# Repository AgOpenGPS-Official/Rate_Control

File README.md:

### [Nano RC12-3](Nano/RC12-3)
- uses a Nano (with ENC28J60 Ethernet shield) & an on-board mounted Cytron for rate control
	- 1 or 2 [MD13S](https://www.cytron.io/p-13amp-6v-30v-dc-motor-driver) for rate control
- self assembled through-hole board, least expensive
- controls two rates
- can be connected to a relay module with a 20 pin cable or dupont connectors
- work switch
- pressure switch
- [OSHPARK]([https://oshpark.com/shared_projects/UU8e90h9](https://oshpark.com/shared_projects/fRBlR1Se)

#
### [Teensy 4.1 RC11-2](Teensy/RC11-2_PCB)
- uses a Teensy & an on-board mounted Cytron for rate control
	- either (1) [MD13S](https://www.cytron.io/p-13amp-6v-30v-dc-motor-driver) for single rate control
 	- or (1) [MDD10A](https://www.cytron.io/p-10amp-5v-30v-dc-motor-driver-2-channels) for dual rate control
- small components are surface mount parts
- Teensy Ethernet 
- can control two rates and eight sections
	- 8 relays (SPDT 12V output)
	- (1) 5V or 12V analog (pressure) input, potentiometer adjustable filtering
	- (2) optically isolated digital (rate/pulse) inputs (5V or 12V)
- 3.3V I2C headers (Qwiic)
	- supports optional external RelayDriver5 I2C board
 - work switch
 - canbus

#
### [ESP32 RC15](ESP32/RC15)
- uses an ESP32 (optional W5500 Ethernet Module)
- mostly surface mount parts
- can control two rates and 7-14 sections
	- (2) DRV8870 motor drivers with reversible outputs for rates
	- (7) DRV8870 motor drivers for either 7 reversible (motorized ball valve) outputs or 14 single ended (high or low) section outputs
- (4) 5V analog inputs (or 2 differential inputs)
- (2) optically isolated digital (rate/pulse) inputs, up to 12V
- RS485 chip & header
- 3.3V I2C header
	- supports optional external RelayDriver5 I2C board

#
### [RelayDriver5](RelayDriver5)
- PCA9535 based I2C IO expander
- designed to plug into 8 or 16 channel relay board with Qwiic cable

#
### Firmware
https://github.com/SK21/AOG_RC

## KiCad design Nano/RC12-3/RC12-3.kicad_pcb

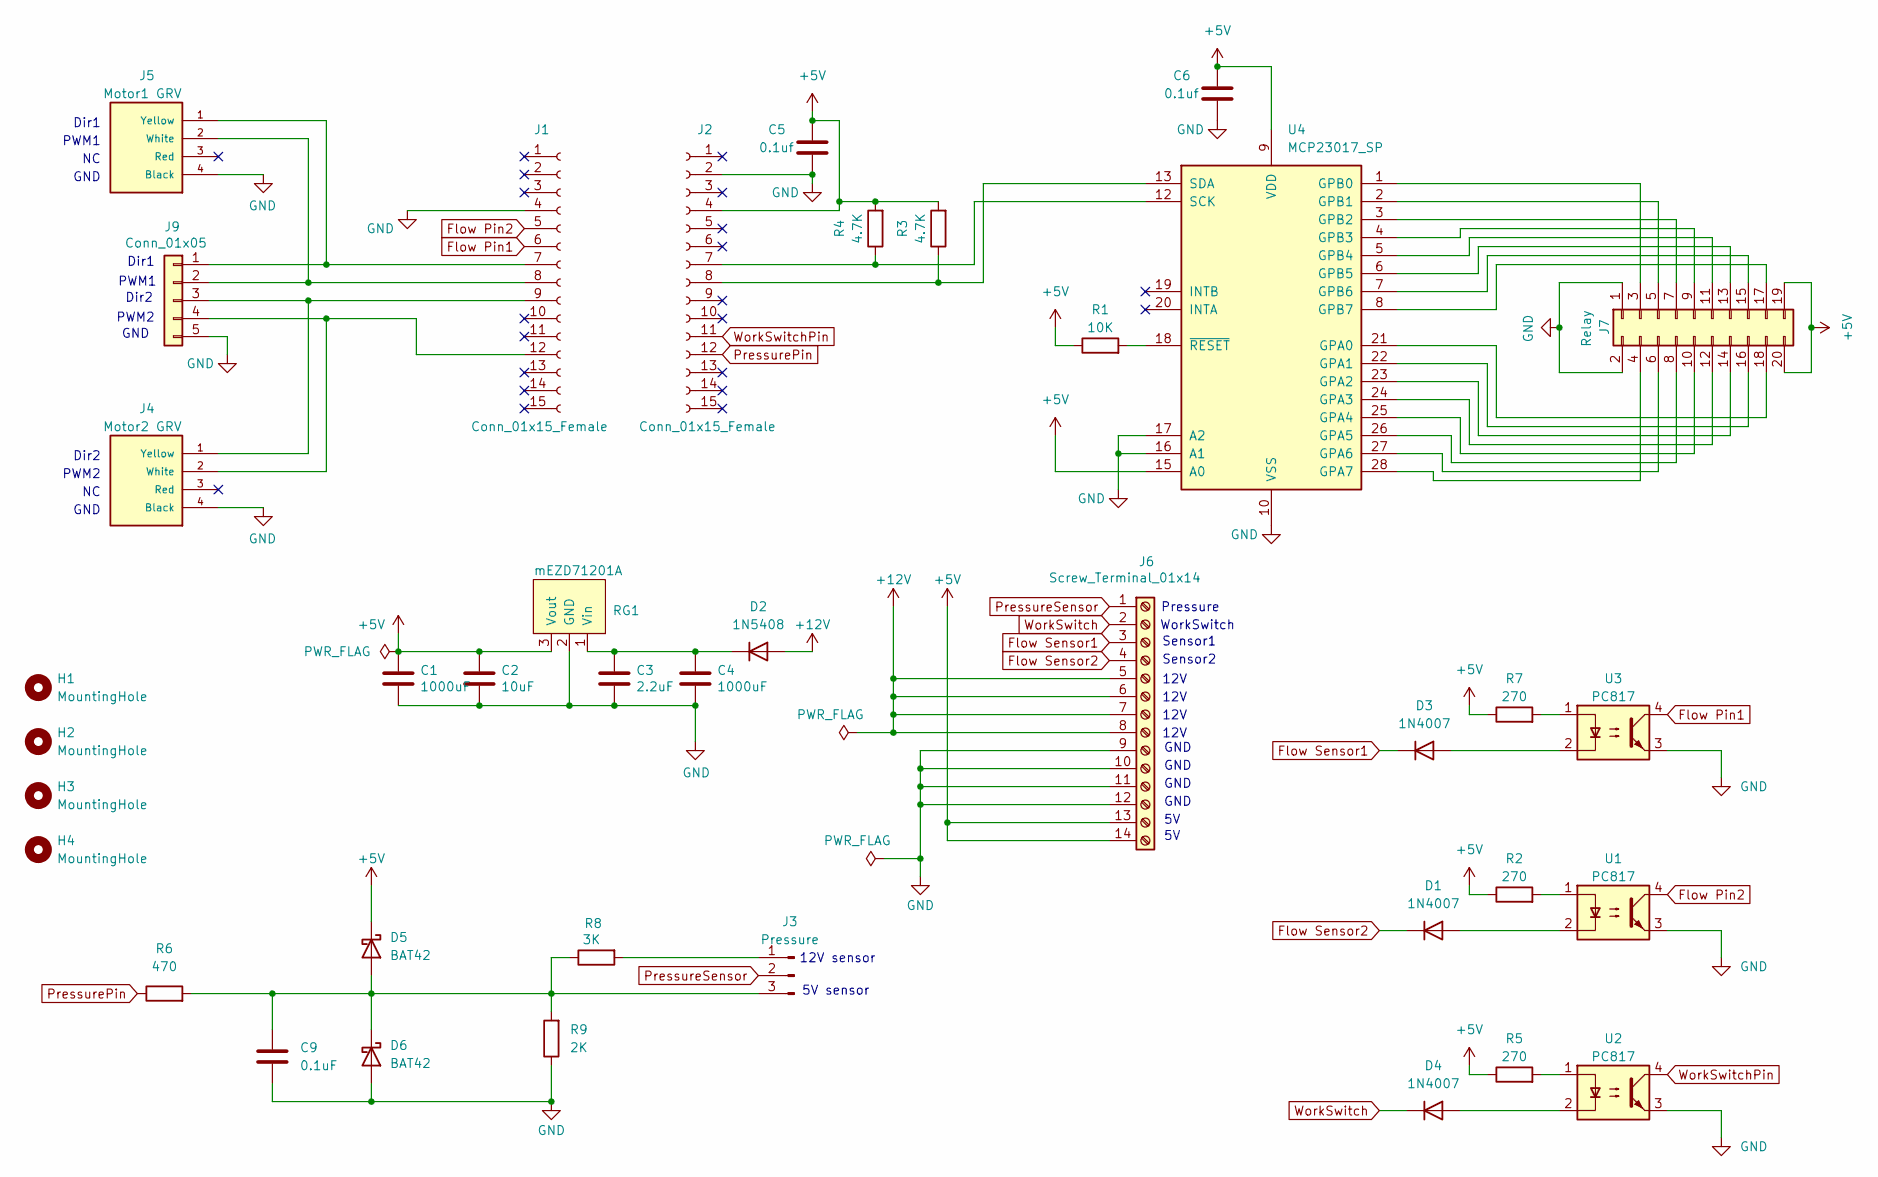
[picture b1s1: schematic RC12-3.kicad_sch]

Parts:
C1, C4: 1000uF; CP_Radial_D10.0mm_P5.00mm
C2: 10uF; C_Disc_D5.0mm_W2.5mm_P2.50mm
C3: 2.2uF; C_Disc_D5.0mm_W2.5mm_P2.50mm
C5, C6: 0.1uf; C_Disc_D5.0mm_W2.5mm_P2.50mm
C9: 0.1uF; C_Disc_D5.0mm_W2.5mm_P2.50mm
D1, D3, D4: 1N4007; D_DO-41_SOD81_P10.16mm_Horizontal
D2: 1N5408
D5, D6: BAT42; D_DO-35_SOD27_P7.62mm_Horizontal
H1, H2, H3, H4: MountingHole; MountingHole_3.2mm_M3
J1, J2: Conn_01x15_Female; PinSocket_1x15_P2.54mm_Vertical
J3: Pressure; PinHeader_1x03_P2.54mm_Vertical
J4: Motor2 GRV; Grove
J5: Motor1 GRV; Grove
J6: Screw_Terminal_01x14; TerminalBlock_Phoenix_PT-1,5-14-5.0-H_1x14_P5.00mm_Horizont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
J7: Relay; PinHeader_2x10_P2.54mm_Vertical
J9: Conn_01x05; Molex_KK-254_AE-6410-05A_1x05_P2.54mm_Vertical
R1: 10K; R_Axial_DIN0207_L6.3mm_D2.5mm_P10.16mm_Horizontal
R2, R5, R7: 270; R_Axial_DIN0207_L6.3mm_D2.5mm_P10.16mm_Horizontal
R3, R4: 4.7K; R_Axial_DIN0207_L6.3mm_D2.5mm_P10.16mm_Horizontal
R6: 470; R_Axial_DIN0207_L6.3mm_D2.5mm_P10.16mm_Horizontal
R8: 3K; R_Axial_DIN0207_L6.3mm_D2.5mm_P10.16mm_Horizontal
R9: 2K; R_Axial_DIN0207_L6.3mm_D2.5mm_P10.16mm_Horizontal
RG1: mEZD71201A
U1, U2, U3: PC817; DIP-4_W7.62mm
U4: MCP23017_SP; DIP-28_W7.62mm

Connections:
+5V: C1.1, C2.1, C5.2, C6.2, D5.1 (K), J2.4, J6.13, J6.14, J7.19, J7.20, R1.1, R2.1, R3.2, R4.2, R5.1, R7.1, RG1.3 (Vout), U4.9 (VDD), U4.15 (A0)
+12V: D2.2 (A), J6.5, J6.6, J6.7, J6.8
Flow Pin1: J1.6, U3.4
Flow Pin2: J1.5, U1.4
Flow Sensor1: D3.1 (K), J6.3
Flow Sensor2: D1.1 (K), J6.4
GND: C1.2, C2.2, C3.2, C4.2, C5.1, C6.1, C9.2, D6.2 (A), J1.4, J2.2, J4.4 (Black), J5.4 (Black), J6.9, J6.10, J6.11, J6.12, J7.1, J7.2, J9.5, R9.1, RG1.2 (GND), U1.3, U2.3, U3.3, U4.10 (VSS), U4.16 (A1), U4.17 (A2)
unnamed: D1.2 (A), U1.2
unnamed: C3.1, C4.1, D2.1 (K), RG1.1 (Vin)
unnamed: D3.2 (A), U3.2
unnamed: D4.2 (A), U2.2
unnamed: C9.1, D5.2 (A), D6.1 (K), J3.3, R6.2, R8.1, R9.2
unnamed: J1.7, J5.1 (Yellow), J9.1
unnamed: J1.8, J5.2 (White), J9.2
unnamed: J1.9, J4.1 (Yellow), J9.3
unnamed: J1.12, J4.2 (White), J9.4
unnamed: J2.7, R4.1, U4.12 (SCK)
unnamed: J2.8, R3.1, U4.13 (SDA)
unnamed: J3.1, R8.2
unnamed: J7.3, U4.1 (GPB0)
unnamed: J7.4, U4.28 (GPA7)
unnamed: J7.5, U4.2 (GPB1)
unnamed: J7.6, U4.27 (GPA6)
unnamed: J7.7, U4.3 (GPB2)
unnamed: J7.8, U4.26 (GPA5)
unnamed: J7.9, U4.4 (GPB3)
unnamed: J7.10, U4.25 (GPA4)
unnamed: J7.11, U4.5 (GPB4)
unnamed: J7.12, U4.24 (GPA3)
unnamed: J7.13, U4.6 (GPB5)
unnamed: J7.14, U4.23 (GPA2)
unnamed: J7.15, U4.7 (GPB6)
unnamed: J7.16, U4.22 (GPA1)
unnamed: J7.17, U4.8 (GPB7)
unnamed: J7.18, U4.21 (GPA0)
unnamed: R2.2, U1.1
unnamed: R5.2, U2.1
unnamed: R7.2, U3.1
unnamed: R1.2, U4.18 (~RESET)
PressurePin: J2.12, R6.1
PressureSensor: J3.2, J6.1
WorkSwitch: D4.1 (K), J6.2
WorkSwitchPin: J2.11, U2.4

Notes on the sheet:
Pressure
GND
PWM1
12V
WorkSwitch
PWM2
Dir1
12V sensor
Dir2
Dir2
5V sensor
Sensor1
Sensor2

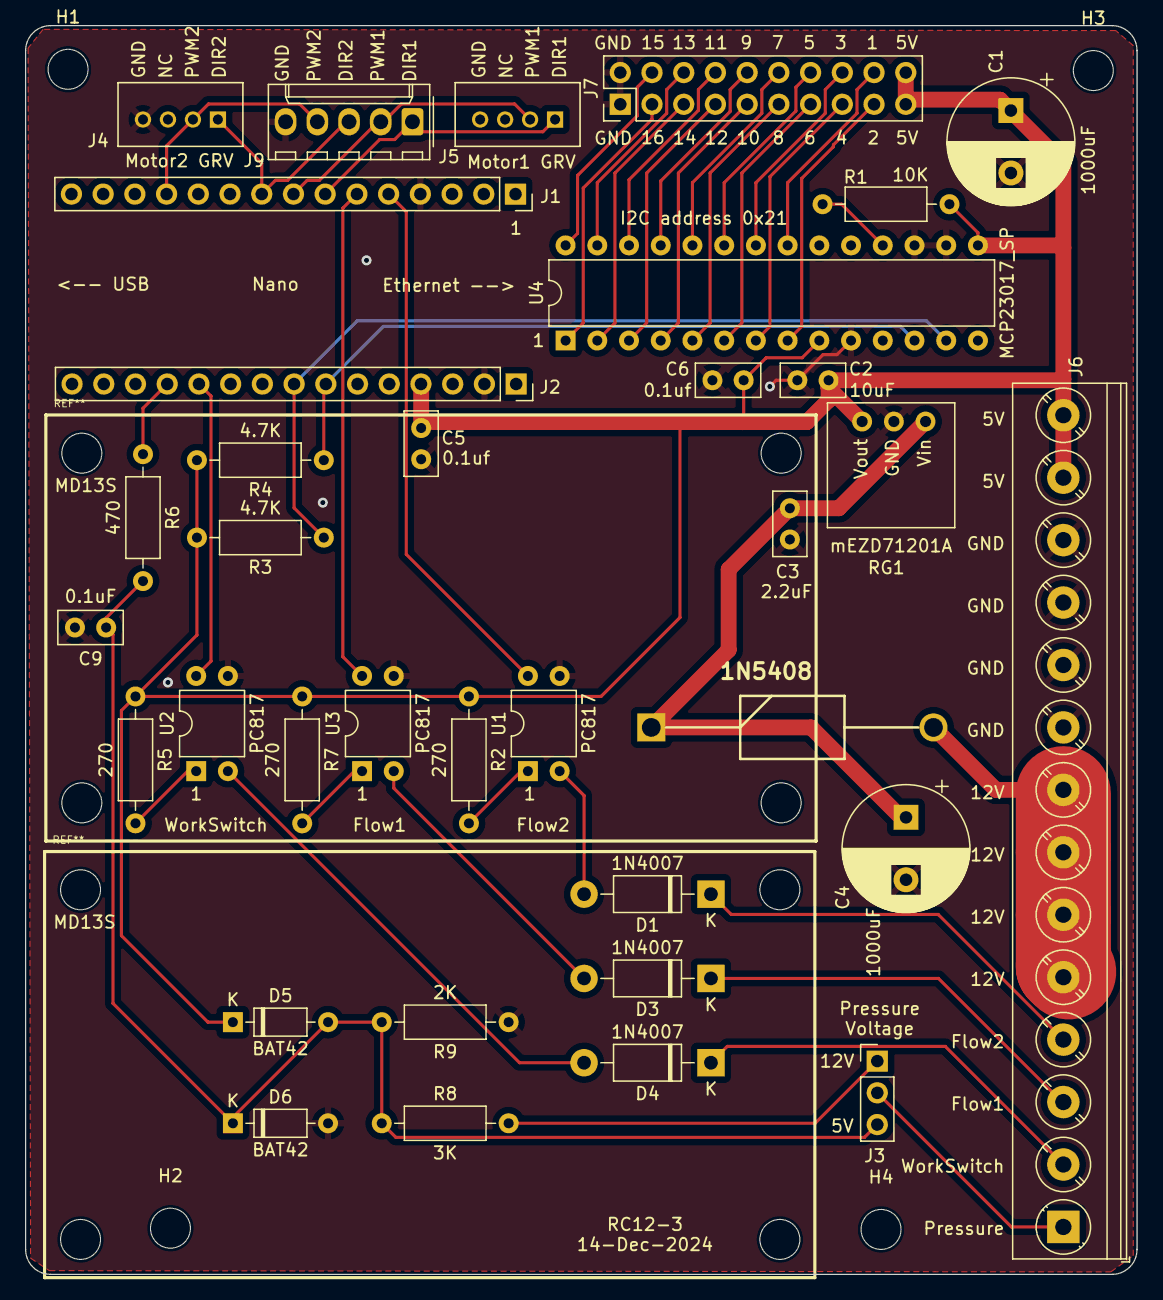
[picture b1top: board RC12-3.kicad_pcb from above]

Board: 2 copper layers, 89.0 x 100.0 mm, 39 parts (0 on the bottom side), 43 nets.

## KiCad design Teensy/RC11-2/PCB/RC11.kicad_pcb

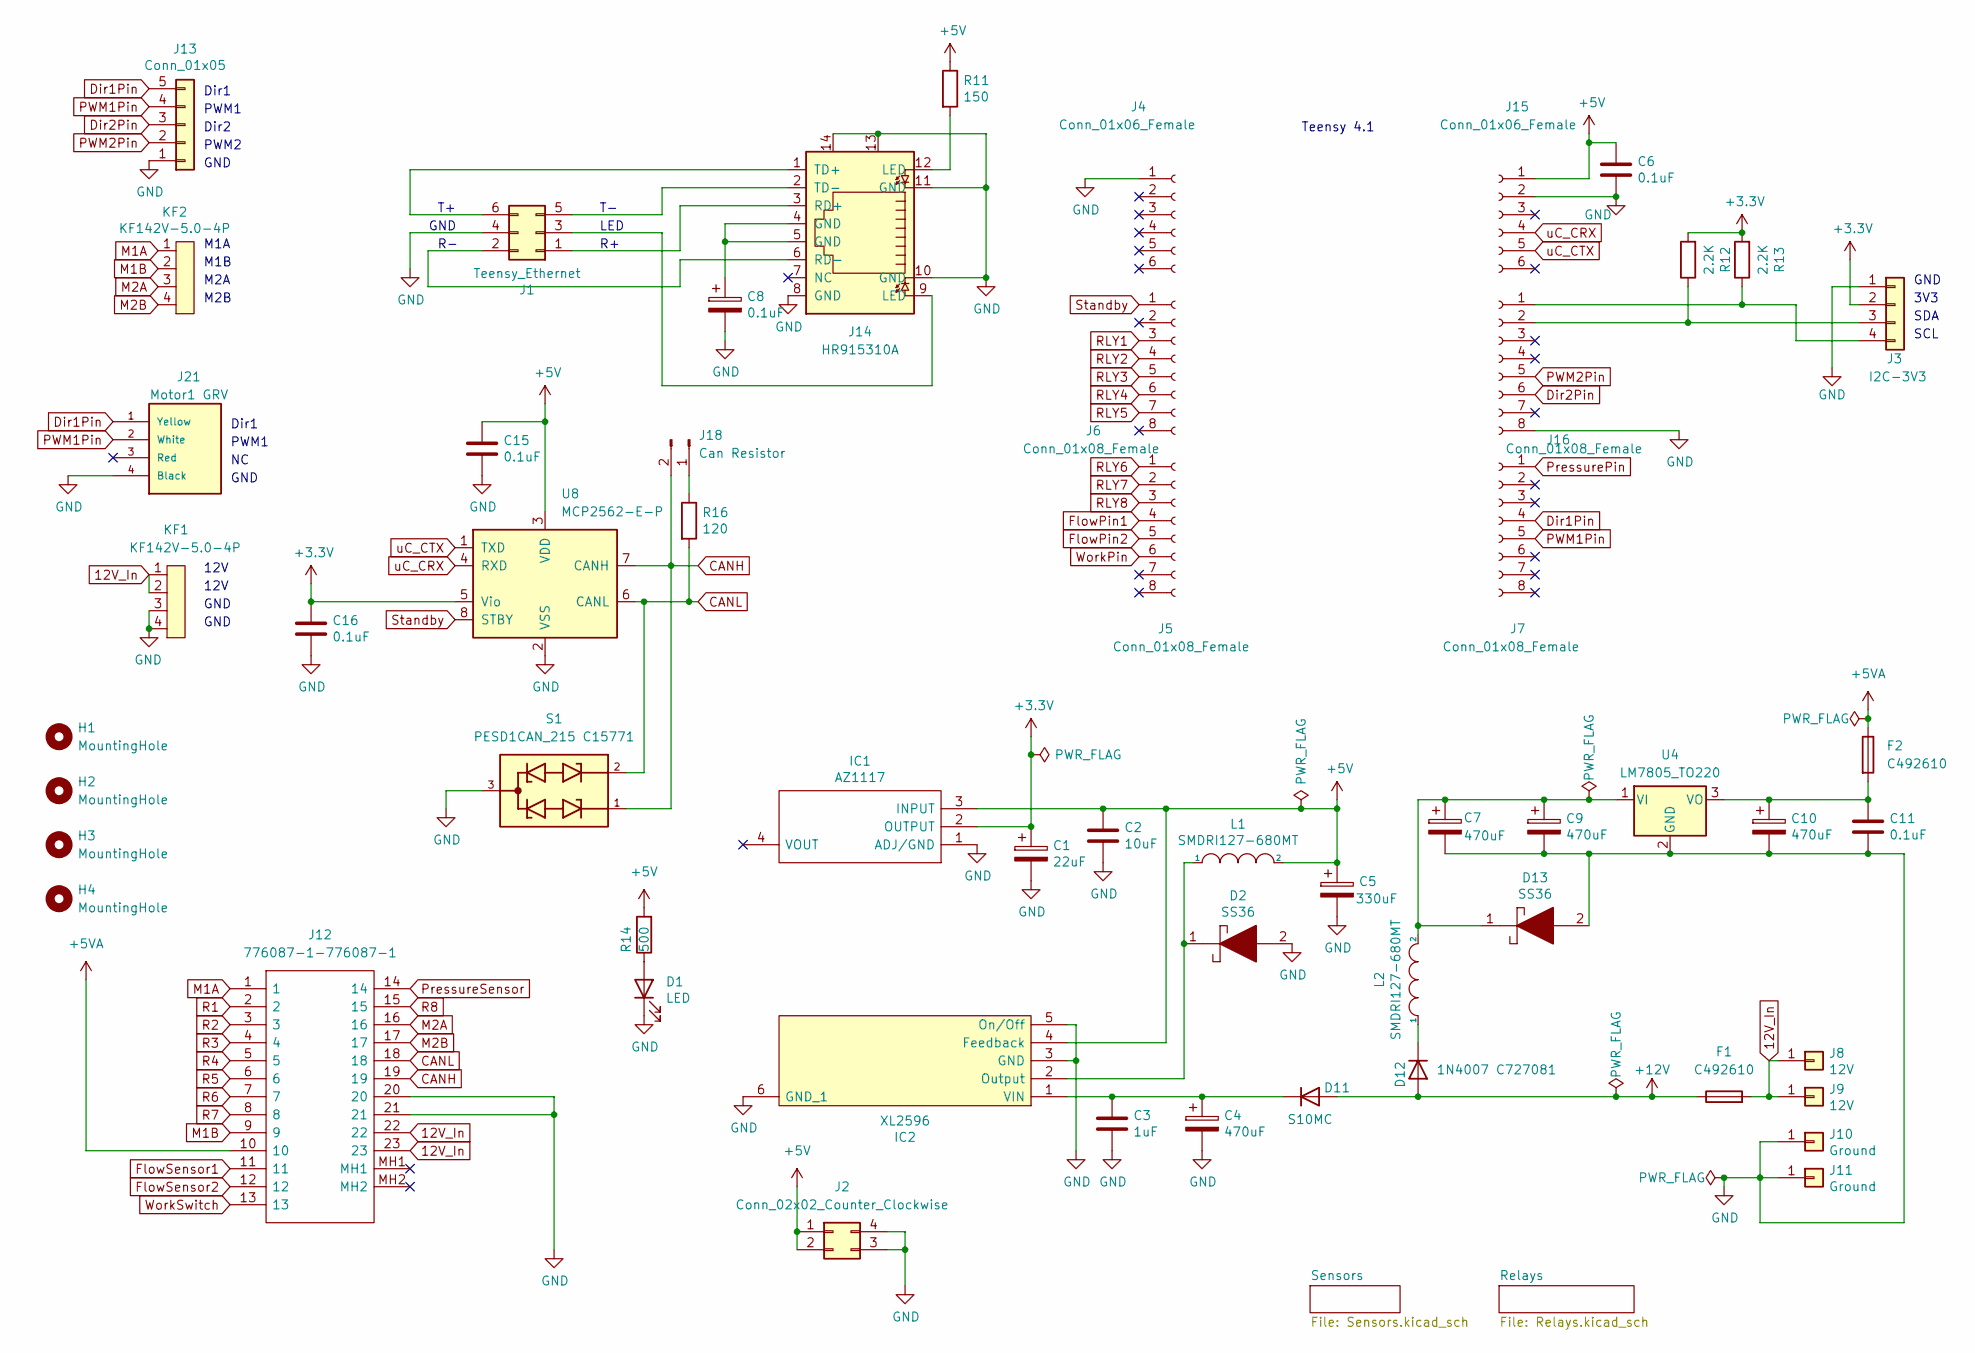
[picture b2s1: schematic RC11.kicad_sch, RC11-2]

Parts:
C1: 22uF; C_0603_1608Metric
C2: 10uF; C_0805_2012Metric
C3: 1uF; C_0805_2012Metric
C4, C7, C9, C10: 470uF; CP_Elec_10x10.5
C5: 330uF; CP_Elec_10x10.5
C6, C8, C11, C15, C16: 0.1uF; C_0603_1608Metric
D1: LED; LED_0603_1608Metric
D2, D13: SS36; SMA(DO-214AC)
D11: S10MC; D_SMC_larger_pads
D12: 1N4007 C727081; SMA(DO-214AC)
F1, F2: C492610; Fuse_Holder_C492610
H1, H2, H3, H4: MountingHole; MountingHole_3.2mm_M3
IC1: AZ1117; SOT230P700X180-4N; Mouser Part Number 621-AZ1117CH-3.3TRG1
IC2: XL2596; TO263-5L
J1: Teensy_Ethernet; PinHeader_2x03_P2.00mm_Vertical
J2: Conn_02x02_Counter_Clockwise; PinSocket_2x02_P2.54mm_Vertical
J3: I2C-3V3; Qwic_vertical
J4, J15: Conn_01x06_Female; PinSocket_1x06_P2.54mm_Vertical
J5, J6, J7, J16: Conn_01x08_Female; PinSocket_1x08_P2.54mm_Vertical
J8: 12V; PowerPinSmall
J9: 12V; PowerPin
J10: Ground; PowerPinSmall
J11: Ground; PowerPin
J12: 776087-1-776087-1; 7760871; Mouser Part Number 571-776087-1
J13: Conn_01x05; Molex_KK-254_AE-6410-05A_1x05_P2.54mm_Vertical
J14: HR915310A; CONN8_HR91531_HAN
J18: Can Resistor; PinHeader_1x02_P2.54mm_Vertical
J21: Motor1 GRV; Grove
KF1, KF2: KF142V-5.0-4P; KF142V-5.08-4P
L1, L2: SMDRI127-680MT; TMPA1265SP-101MN-D
R11: 150; R_0603_1608Metric
R12, R13: 2.2K; R_0603_1608Metric
R14: 500; R_0603_1608Metric
R16: 120; R_0603_1608Metric
S1: PESD1CAN_215 C15771; DIO_PESD1CAN_215
U4: LM7805_TO220; TO-220-3_Vertical
U8: MCP2562-E-P; DIP-8_W7.62mm

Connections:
12V_In: F1.2, J8.1, J9.1, J12.22, J12.23, KF1.1, KF1.2
+3.3V: C1.1, C16.1, IC1.2 (OUTPUT), J3.2, R12.2, R13.2, U8.5 (Vio); also elsewhere on the board
+5V: C2.1, C5.1, C6.1, C15.1, IC1.3 (INPUT), IC2.4 (Feedback), J2.1, J2.2, J15.1, L1.2, R11.1, R14.2, U8.3 (VDD); also elsewhere on the board
+5VA: F2.1, J12.10; also elsewhere on the board
+12V: D11.2 (A), D12.2 (A), F1.1; also elsewhere on the board
CANH: J12.19, J18.2, S1.1, U8.7 (CANH)
CANL: J12.18, R16.2, S1.2, U8.6 (CANL)
Dir1Pin: J7.4, J13.5, J21.1 (Yellow)
Dir2Pin: J13.3, J16.6
FlowPin1: J5.4; also elsewhere on the board
FlowPin2: J5.5; also elsewhere on the board
FlowSensor1: J12.11; also elsewhere on the board
FlowSensor2: J12.12; also elsewhere on the board
GND: C1.2, C2.2, C3.2, C4.2, C5.2, C6.2, C7.2, C8.2, C9.2, C10.2, C11.2, C15.2, C16.2, D1.1 (K), D2.2, D13.2, IC1.1 (ADJ/GND), IC2.3 (GND), IC2.5 (On/Off), IC2.6 (GND_1), J1.4, J2.3, J2.4, J3.1, J4.1, J10.1, J11.1, J12.20, J12.21, J13.1, J14.8 (GND), J14.10 (GND), J14.11 (GND), J14.13, J14.14, J15.2, J16.8, J21.4 (Black), KF1.3, KF1.4, S1.3, U4.2 (GND), U8.2 (VSS); also elsewhere on the board
M1A: J12.1, KF2.1
M1B: J12.9, KF2.2
M2A: J12.16, KF2.3
M2B: J12.17, KF2.4
unnamed: C8.1, J14.4 (GND), J14.5 (GND)
unnamed: D1.2 (A), R14.1
unnamed: C3.1, C4.1, D11.1 (K), IC2.1 (VIN)
unnamed: D12.1 (K), L2.1
unnamed: D2.1, IC2.2 (Output), L1.1
unnamed: J1.1, J14.3 (RD+)
unnamed: J1.2, J14.6 (RD-)
unnamed: J1.3, J14.9 (LED)
unnamed: J1.5, J14.2 (TD-)
unnamed: J1.6, J14.1 (TD+)
unnamed: J14.12 (LED), R11.2
unnamed: J3.4, J16.1, R13.1
unnamed: J3.3, J16.2, R12.1
unnamed: J18.1, R16.1
unnamed: C7.1, C9.1, D13.1, L2.2, U4.1 (VI)
unnamed: C10.1, C11.1, F2.2, U4.3 (VO)
PWM1Pin: J7.5, J13.4, J21.2 (White)
PWM2Pin: J13.2, J16.5
PressurePin: J7.1; also elsewhere on the board
PressureSensor: J12.14; also elsewhere on the board
R1: J12.2; also elsewhere on the board
R2: J12.3; also elsewhere on the board
R3: J12.4; also elsewhere on the board
R4: J12.5; also elsewhere on the board
R5: J12.6; also elsewhere on the board
R6: J12.7; also elsewhere on the board
R7: J12.8; also elsewhere on the board
R8: J12.15; also elsewhere on the board
RLY1: J6.3; also elsewhere on the board
RLY2: J6.4; also elsewhere on the board
RLY3: J6.5; also elsewhere on the board
RLY4: J6.6; also elsewhere on the board
RLY5: J6.7; also elsewhere on the board
RLY6: J5.1; also elsewhere on the board
RLY7: J5.2; also elsewhere on the board
RLY8: J5.3; also elsewhere on the board
Standby: J6.1, U8.8 (STBY)
WorkPin: J5.6; also elsewhere on the board
WorkSwitch: J12.13; also elsewhere on the board
uC_CRX: J15.4, U8.4 (RXD)
uC_CTX: J15.5, U8.1 (TXD)

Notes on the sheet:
GND
Dir2
Dir1
M2A
PWM1
PWM1
M1B
M2B
SCL
LED
Teensy 4.1
PWM2
12V
SDA
M1A
3V3

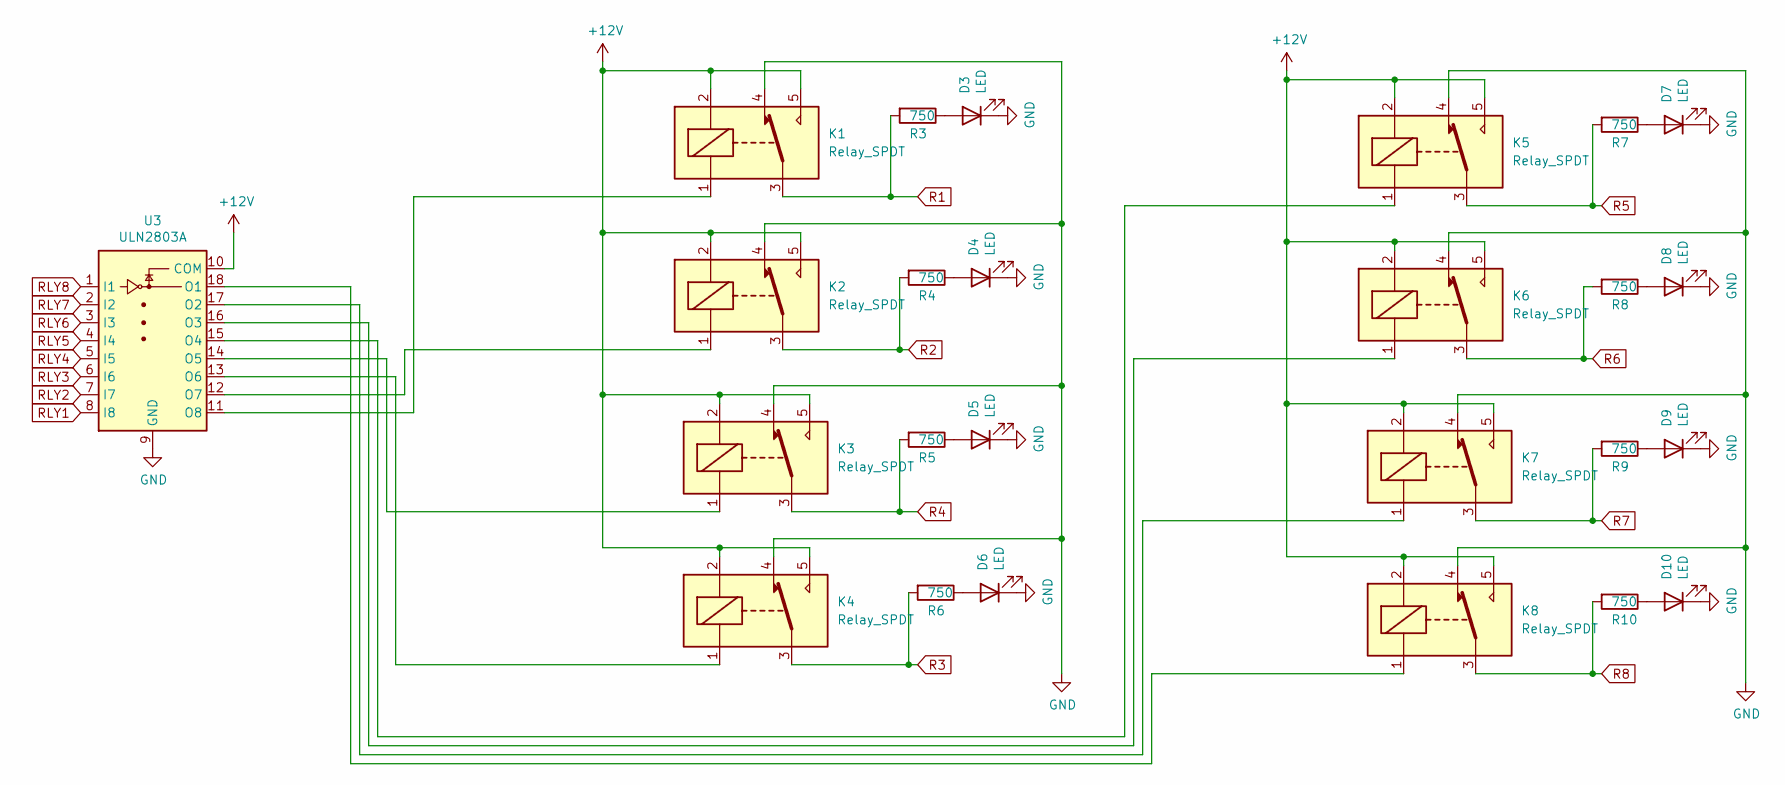
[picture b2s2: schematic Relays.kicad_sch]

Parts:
D3, D4, D5, D6, D7, D8, D9, D10: LED; LED_0603_1608Metric
K1, K2, K3, K4, K5, K6, K7, K8: Relay_SPDT; Songle_SRD-05VDC-SL-C
R3, R4, R5, R6, R7, R8, R9, R10: 750; R_0603_1608Metric
U3: ULN2803A

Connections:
+12V: K1.2, K1.5, K2.2, K2.5, K3.2, K3.5, K4.2, K4.5, K5.2, K5.5, K6.2, K6.5, K7.2, K7.5, K8.2, K8.5, U3.10 (COM); also elsewhere on the board
GND: D3.1 (K), D4.1 (K), D5.1 (K), D6.1 (K), D7.1 (K), D8.1 (K), D9.1 (K), D10.1 (K), K1.4, K2.4, K3.4, K4.4, K5.4, K6.4, K7.4, K8.4, U3.9 (GND); also elsewhere on the board
unnamed: D3.2 (A), R3.1
unnamed: D4.2 (A), R4.1
unnamed: D5.2 (A), R5.1
unnamed: D6.2 (A), R6.1
unnamed: D7.2 (A), R7.1
unnamed: D8.2 (A), R8.1
unnamed: D9.2 (A), R9.1
unnamed: D10.2 (A), R10.1
unnamed: K8.1, U3.18 (O1)
unnamed: K7.1, U3.17 (O2)
unnamed: K6.1, U3.16 (O3)
unnamed: K5.1, U3.15 (O4)
unnamed: K3.1, U3.14 (O5)
unnamed: K4.1, U3.13 (O6)
unnamed: K2.1, U3.12 (O7)
unnamed: K1.1, U3.11 (O8)
R1: K1.3, R3.2; also elsewhere on the board
R2: K2.3, R4.2; also elsewhere on the board
R3: K4.3, R6.2; also elsewhere on the board
R4: K3.3, R5.2; also elsewhere on the board
R5: K5.3, R7.2; also elsewhere on the board
R6: K6.3, R8.2; also elsewhere on the board
R7: K7.3, R9.2; also elsewhere on the board
R8: K8.3, R10.2; also elsewhere on the board
RLY1: U3.8 (I8); also elsewhere on the board
RLY2: U3.7 (I7); also elsewhere on the board
RLY3: U3.6 (I6); also elsewhere on the board
RLY4: U3.5 (I5); also elsewhere on the board
RLY5: U3.4 (I4); also elsewhere on the board
RLY6: U3.3 (I3); also elsewhere on the board
RLY7: U3.2 (I2); also elsewhere on the board
RLY8: U3.1 (I1); also elsewhere on the board

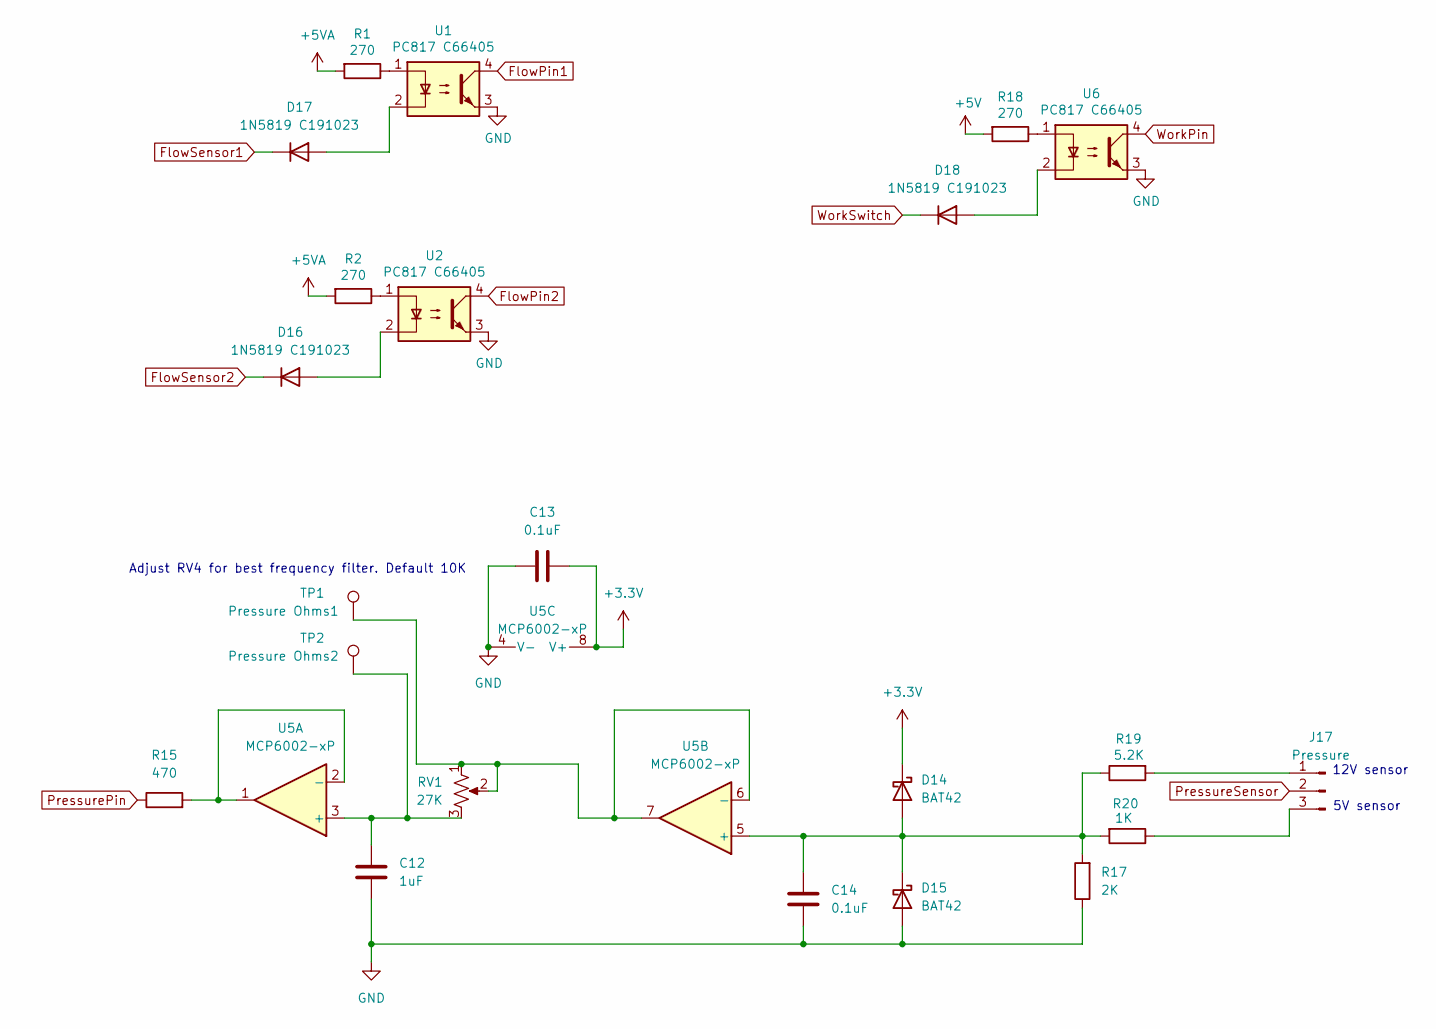
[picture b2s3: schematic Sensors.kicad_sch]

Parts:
C12: 1uF; C_0805_2012Metric
C13, C14: 0.1uF; C_0603_1608Metric
D14, D15: BAT42; D_SOD-123
D16, D17, D18: 1N5819 C191023; 1N5819
J17: Pressure; PinHeader_1x03_P2.54mm_Vertical
R1, R2, R18: 270; R_0603_1608Metric
R15: 470; C_0603_1608Metric
R17: 2K; R_0603_1608Metric
R19: 5.2K; R_0603_1608Metric
R20: 1K; R_0603_1608Metric
RV1: 27K; Potentiometer
TP1: Pressure Ohms1; TestPoint_THTPad_D2.5mm_Drill1.2mm
TP2: Pressure Ohms2; TestPoint_THTPad_D2.5mm_Drill1.2mm
U1, U2, U6: PC817 C66405; SMD-4_4.6x7.62mm_P2.54mm
U5: MCP6002-xP; SOIC127P600X175-8N

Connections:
+3.3V: C13.2, D14.1 (K), U5.8 (V+); also elsewhere on the board
+5V: R18.2; also elsewhere on the board
+5VA: R1.2, R2.2; also elsewhere on the board
FlowPin1: U1.4; also elsewhere on the board
FlowPin2: U2.4; also elsewhere on the board
FlowSensor1: D17.1 (K); also elsewhere on the board
FlowSensor2: D16.1 (K); also elsewhere on the board
GND: C12.2, C13.1, C14.2, D15.2 (A), R17.1, U1.3, U2.3, U5.4 (V-), U6.3; also elsewhere on the board
unnamed: C14.1, D14.2 (A), D15.1 (K), R17.2, R19.1, R20.2, U5.5 (+)
unnamed: D16.2 (A), U2.2
unnamed: D17.2 (A), U1.2
unnamed: D18.2 (A), U6.2
unnamed: J17.1, R19.2
unnamed: J17.3, R20.1
unnamed: R1.1, U1.1
unnamed: R2.1, U2.1
unnamed: R18.1, U6.1
unnamed: C12.1, RV1.3, TP2.1, U5.3 (+)
unnamed: R15.2, U5.1, U5.2 (-)
unnamed: RV1.1, RV1.2, TP1.1, U5.6 (-), U5.7
PressurePin: R15.1; also elsewhere on the board
PressureSensor: J17.2; also elsewhere on the board
WorkPin: U6.4; also elsewhere on the board
WorkSwitch: D18.1 (K); also elsewhere on the board

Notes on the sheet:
5V sensor
Adjust RV4 for best frequency filter. Default 10K
12V sensor

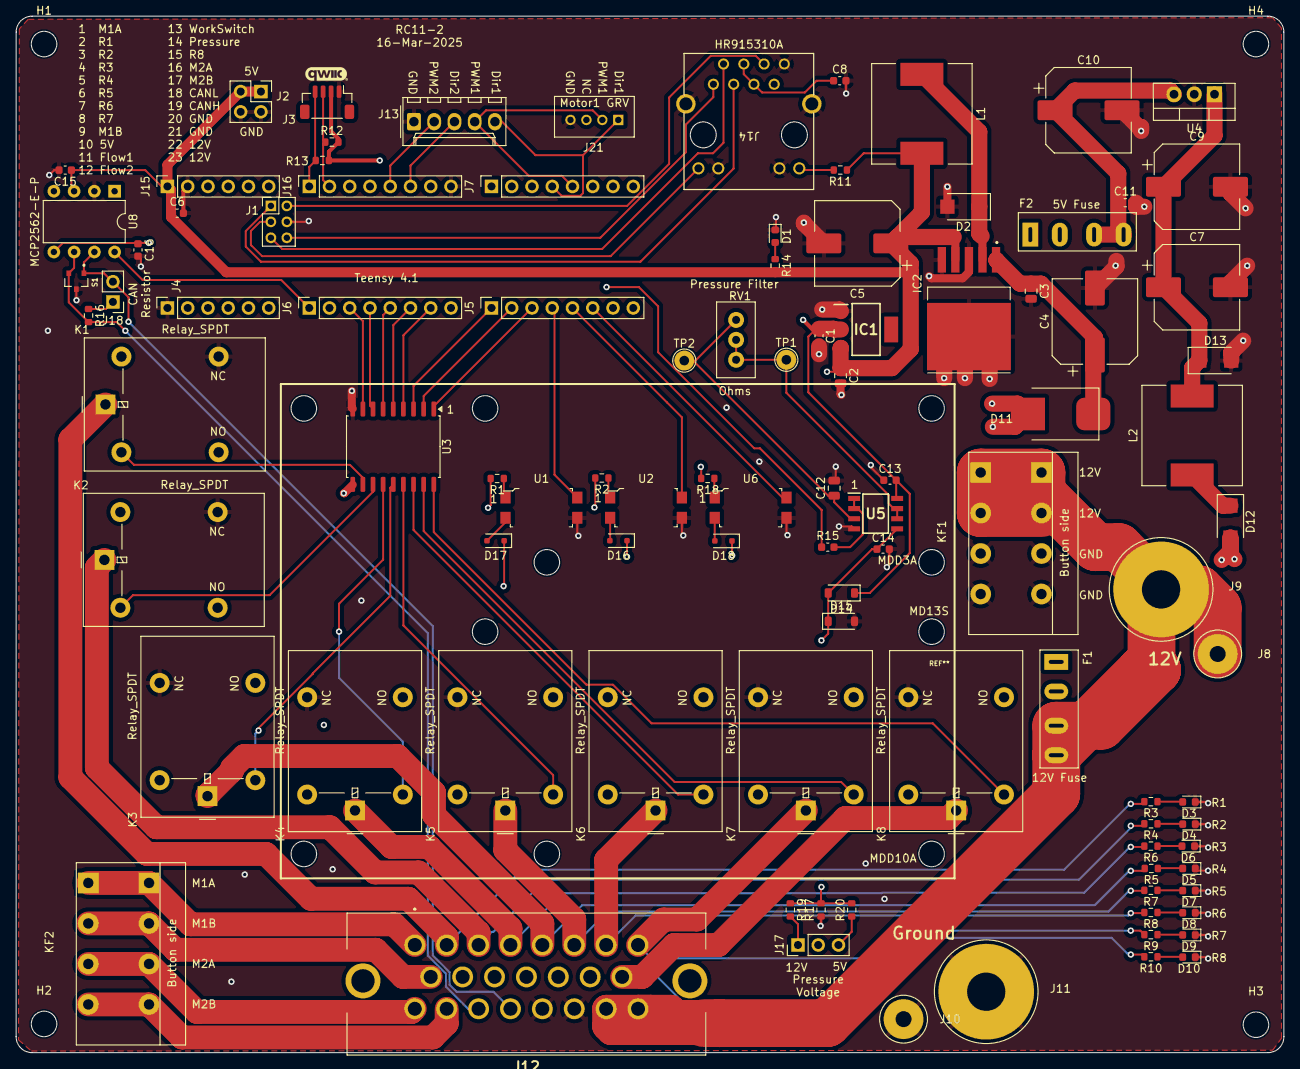
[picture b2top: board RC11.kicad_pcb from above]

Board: 4 copper layers, 159.0 x 130.0 mm, 104 parts (0 on the bottom side), 87 nets.

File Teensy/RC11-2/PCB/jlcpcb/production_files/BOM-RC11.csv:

Comment,Designator,Footprint,LCSC,Quantity
AZ1117,IC1,SOT230P700X180-4N,C110474,1
27K,RV1,Potentiometer,C118932,1
0.1uF,"C11,C13,C14,C15,C16,C6,C8",C_0603_1608Metric,C14663,7
PESD1CAN_215  C15771,S1,DIO_PESD1CAN_215,C15771,1
10uF,C2,C_0805_2012Metric,C15850,1
I2C-3V3,J3,Qwic_vertical,C160390,1
S10MC,D11,D_SMC_larger_pads,C169472,1
1N5819  C191023,"D16,D17,D18",1N5819,C191023,3
120,R16,R_0603_1608Metric,C22787,1
150,R11,R_0603_1608Metric,C22808,1
LED,"D1,D10,D3,D4,D5,D6,D7,D8,D9",LED_0603_1608Metric,C2286,9
270,"R1,R18,R2",R_0603_1608Metric,C22966,3
2K,R17,R_0603_1608Metric,C22975,1
470,R15,C_0603_1608Metric,C23179,1
500,R14,R_0603_1608Metric,C23193,1
750,"R10,R3,R4,R5,R6,R7,R8,R9",R_0603_1608Metric,C23253,8
Conn_01x08_Female,"J16,J5,J6,J7",PinSocket_1x08_P2.54mm_Vertical,C27438,4
HR915310A,J14,CONN8_HR91531_HAN,C2760326,1
5.2K,R19,R_0603_1608Metric,C2828621,1
1uF,"C12,C3",C_0805_2012Metric,C28323,2
470uF,"C10,C4,C7,C9",CP_Elec_10x10.5,C2836436,4
SS36,"D13,D2",SMA(DO-214AC),C2903825,2
1K,R20,R_0603_1608Metric,C2907113,1
Pressure,J17,PinHeader_1x03_P2.54mm_Vertical,C2937625,1
Conn_02x02_Counter_Clockwise,J2,PinSocket_2x02_P2.54mm_Vertical,C2977590,1
Relay_SPDT,"K1,K2,K3,K4,K5,K6,K7,K8",Songle_SRD-05VDC-SL-C,C30431,8
MCP2562-E-P,U8,DIP-8_W7.62mm,C305904,1
776087-1-776087-1,J12,7760871,C378893,1
Motor1 GRV,J21,Grove,C403774,1
Conn_01x06_Female,"J15,J4",PinSocket_1x06_P2.54mm_Vertical,C40877,2
2.2K,"R12,R13",R_0603_1608Metric,C4190,2
KF142V-5.0-4P,"KF1,KF2",KF142V-5.08-4P,C475136,2
Can Resistor,J18,PinHeader_1x02_P2.54mm_Vertical,C492401,1
C492610,"F1,F2",Fuse_Holder_C492610,C492610,2
330uF,C5,CP_Elec_10x10.5,C5162354,1
LM7805_TO220,U4,TO-220-3_Vertical,C5444281,1
BAT42,"D14,D15",D_SOD-123,C5805639,2
22uF,C1,C_0603_1608Metric,C59461,1
PC817  C66405,"U1,U2,U6",SMD-4_4.6x7.62mm_P2.54mm,C66405,3
1N4007   C727081,D12,SMA(DO-214AC),C727081,1
MCP6002-xP,U5,SOIC127P600X175-8N,C7377,1
XL2596,IC2,TO263-5L,C74190,1
ULN2803A,U3,ULN2803A,C845537,1
Conn_01x05,J13,Molex_KK-254_AE-6410-05A_1x05_P2.54mm_Vertical,C86505,1
SMDRI127-680MT,"L1,L2",TMPA1265SP-101MN-D,C9907,2
12V,J8,PowerPinSmall,,1
Ground,J11,PowerPin,,1
12V,J9,PowerPin,,1
Ground,J10,PowerPinSmall,,1
Pressure Ohms1,TP1,TestPoint_THTPad_D2.5mm_Drill1.2mm,,1
Pressure Ohms2,TP2,TestPoint_THTPad_D2.5mm_Drill1.2mm,,1
Teensy_Ethernet,J1,PinHeader_2x03_P2.00mm_Vertical,,1

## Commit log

2025-03-31 update RC11
2025-04-07 update nano board
